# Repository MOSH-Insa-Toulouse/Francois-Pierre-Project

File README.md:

# Francois-Pierre-Project
## Projet capteur graphene
Projet de 4ème année Génie Physique, à l'INSA de Toulouse. Réalisation d'un capteur graphene de déformation. Le but est de mesurer la résistance et la tension du graphene sur une feuille de papier. Pour ce faire nous avons élaborer un capteur accessible à tous et simple d'utilisation sur arduino et App Inventor. Dans ce Git vous trouverez toute les ressources et information nécessaire pour comprendre le fonctionnement de notre capteur et pouvoir le réaliser chez vous.

## Sommaire

  - [1. Matériel requis](#1-Matériel-requis)
  - [2. Kicad](#2-Kicad)
      - [2.1 Création des empreintes et des composants](#21-Création-des-empreintes-et-des-composants)
      - [2.2 Création du PCB](#22-Création-du-PCB)
  - [3. Code Arduino](#3-code-arduino)
      - [3.1 Librairies utilisées](#31-Librairies-utilisées)
      - [3.2 Le code](#32-Le-code)
  - [4. Application Bluetooth](#4-application-Bluetooth)
  - [5. Banc de test](#5-Banc-de-test)
      - [5.1 Fonctionnement du banc](#51-Fonctionnement-du-banc)
      - [5.2 Code arduino](#52-Code-arduino)
  - [6. Datasheet](#6-datasheet)
  - [7. Contacte](#6-Contacte)

## 1. Matériel requis  

- Smartphone Androide 
- Carte Arduino Uno [info](https://www.arduino-france.com/review/arduino-uno/)
- Une plaque de cuivre pour shield. Ou bien des câbles de connexions
- Papier
- Crayon de papier
- Un module HC-05 (gestion du Bluetooth) [ici](https://fr.aliexpress.com/item/32496218488.html?src=google&albch=shopping&acnt=248-630-5778&isdl=y&slnk=&plac=&mtctp=&albbt=Google_7_shopping&aff_platform=google&aff_short_key=UneMJZVf&&albagn=888888&isSmbAutoCall=false&needSmbHouyi=false&albcp=11565796786&albag=115683794594&trgt=800756788306&crea=fr32496218488&netw=u&device=c&albpg=800756788306&albpd=fr32496218488&gclid=CjwKCAjwr_uCBhAFEiwAX8YJgRBUgtCF6S3dou6QC6xu91THwD-LvObxEluNS2bU644OLQE_p05mxxoCGZEQAvD_BwE&gclsrc=aw.ds)
- Un écran OLED [ici](https://www.google.com/aclk?sa=l&ai=DChcSEwjiwND8ltHvAhVc6u0KHTwOD0wYABAGGgJkZw&sig=AOD64_0E9f4FFmKPCGubT07_igBVagq6Cw&ctype=5&q=&ved=2ahUKEwi72sj8ltHvAhUSmRQKHRkPB9IQ9aACegQIARBK&adurl=)
- Un encodeur rotatif [ici](https://www.google.com/aclk?sa=l&ai=DChcSEwi_u8-dl9HvAhXC7e0KHZQrC94YABAEGgJkZw&sig=AOD64_0jWmans1feAKcjE1r1Iod4QknEqw&ctype=5&q=&ved=2ahUKEwi5kcadl9HvAhWl8uAKHZ9SAuUQ9aACegQIARBg&adurl=)
- Deux pince crocodile en cuivre
- Un transistor LTC1050 [ici](https://www.reichelt.com/fr/fr/amplificateurs-op-rationnels-unique-2-5-mhz-dil-8-ltc-1050-cn8-p10921.html) 

## 2. Kicad 

Kicad est un logiciel de conception pour l'électronique. Il permet de créer des schémas de circuit, visualiser des circuits en 3D, associer des empreintes au circuit. Dans notre cas, nous utilisons Kicad pour créer un shield pour notre carte Arduino Uno. Ce shield va nous permettre de monter nos composant directement sur la carte. Toute nos empreintes et plans de notre shield sont disponible dans [notre GIT](https://github.com/MOSH-Insa-Toulouse/Francois-Pierre-Project/tree/main/Shield)  

### 2.1 Création des empreintes et des composants

- Pour réaliser notre shield, nous avons dû créer une librairie d'empreinte pour nos composants. En effet ceux-ci n'étant pas disponible sur les librairies de Kicad nous avons donc créés des schémas et empreintes pour tous nos modules.

- *Capteur Graphite*

- *HC-05*

- *Encodeur Rotatoire*

- *OLED*

- *LTC1050*

### 2.2 Création du PCB

- Une fois les empreintes et les schématiques crées nous avons pu réaliser la schématique complète du circuit. Dans ce schéma vous pouvez retrouver nos modules ainsi que des composants éléctronique de base.

- *Schéma de notre circuit*

- Une fois la schématique finis nous avons pu allouer à chaque composants (résistance, capacité...) une empreinte. Nous avons ensuite visualisé sur l'éditeur de circuit imprimé notre PCB. Nous avons donc organisé nos composant pour qu'il tiennent sur le shield et que nous puissons router correctement et sur chaque pin les différents modules.

- Pour être sur du résultat que nous voulions nous avons pu visulaiser sur Gerber notre shield en 3D avec les composant dessus, à l'execption des module bluetooth, de l'encodeur, du capteur et du LTC qui n'ont pas d'empreinte 3D.

## 3. Code Arduino

### 3.1 Librairies utilisées

- Pour réaliser notre capteur, nous utilisons [trois librairies](https://github.com/MOSH-Insa-Toulouse/Francois-Pierre-Project/tree/main/Libairies%20Arduino). 
- La librairie ["Adafruit_BusIO"](https://github.com/MOSH-Insa-Toulouse/Francois-Pierre-Project/tree/main/Libairies%20Arduino/Adafruit_BusIO) qui permet de gérer le connexions en I2C et SPI
- Les librairies ["Adafruit_GFX_Library"](https://github.com/MOSH-Insa-Toulouse/Francois-Pierre-Project/tree/main/Libairies%20Arduino/Adafruit_GFX_Library) et ["Adafruit_SSD1306"](https://github.com/MOSH-Insa-Toulouse/Francois-Pierre-Project/tree/main/Libairies%20Arduino/Adafruit_SSD1306)qui permet de gérer notre écran OLED.

### 3.2 Le code

- [Le code arduino](https://github.com/MOSH-Insa-Toulouse/Francois-Pierre-Project/tree/main/Code-Capteur-Graphite) permet de gérer le capteur. Il récupère sur le pin analogique A0 la valeur de la tension du capteur. Grace à une analyse du circuit électronique, nous pouvons déterminer la résistance en fonction de cette tension. Le code affiche sur un écran OLED différents menus en fonction de si l'on appuie ou non sur l'encodeur rotatoire. Il y a un delay de 5ms entre chaque lecture analogique.

## 4. Application Bluetooth

- [L'application](https://github.com/MOSH-Insa-Toulouse/Francois-Pierre-Project/blob/main/TP5.apk) permet de recevoir sur le téléphone la mesure de la résistance et de la tension délivré par le capteur. Nous affichons les deux donnés et nous traçons un graphique de la variation de résistance avec une échelle ajustable. La carte Arduino et plus précisément le module Bluetooth envoie un octet de donnée au téléphone via les pins TX et RX. Cet octet contient à la fois des valeurs de résistance et de tension séparés par de ",". Chaque doublet de valeurs est lui séparé par des ";". Notre téléphone reçois donc "49,0.39;35,0.60;70,0.37" avec d'abord la valeur de résistance puis une valeur de tension. Le téléphone sépare donc chaque valeur et les affiches. Notre application traite les données sur un intervalle de 100ms. 

- *Code de l'application qui permet de séparer l'octet reçu et de séparer tension et résistance*

- Notre code a aussi une fonctionnalité qui enlève les variations trop importantes de résistance. En effet lors de nos tests notre téléphone recevait bien les valeurs affichées par le OLED, seulement nous avions aussi des valeurs intempestives qui ne correspondaient pas à une mesure (entre 1 et 9). Pour pallier ce problème, nous avons donc décider de ne pas prendre en compte les variations trop importantes.

- Pour finir nous avons rajouté une fonctionnalité qui permet à l'utilisateur de zoomer ou dezoomer sur le graphique.

- *Code APK permettant de Rescale le graphique*

- La face avant de notre application permet de choisir un module Bluetooth auquel se connecter (Cadre rouge), puis de régler l'échelle (bleu), de visualiser la variation de résistance (marron), et d'avoir les valeurs de résistance et tension en temps réelle (vert).

- *Face avant de notre application*

## 5. Banc de test

- Le banc de test est réalisé sur le logiciel de CAO FreeCad. Il nous est utile pour remplacer le banc de test initiale qui endommage et plie de manière irréversible la jauge de graphite. Le banc de test que nous avons imaginé permettrait donc de ré utiliser la même jauge plusieurs fois car celle-ci ne serait pas endommagé par les tests. Les fichier stl pour impression 3D sont [ici](https://github.com/MOSH-Insa-Toulouse/Francois-Pierre-Project/tree/main/Banc%20de%20test).

### 5.1 Fonctionnement du banc

- Le banc de test que nous avons imaginé permet de mesurer la déformation du capteur sans avoir à le toucher. Il est constitué de deux partie, le socle et la barre. Le servomoteur vient se positionner dans l'extrusion de la barre. Le disque présent sur l'autre côté vient lui se placer dans l'encoche du socle. Les pince crocodile ainsi que la jauge sont immobile grâce à l'encadrement dans lequel ils viennent s'insérer. Le servomoteur vient donc faire tourner la barre de bas en haut et nous récupérons les valeurs de résistances sur le terminal ou dans le fichier txt de notre téléphone.

- 
- 

- A l'inverse du banc de test initiale celui que nous avons imaginé n'a pas un rayon de courbure définis et connus. En revanche il est possible de connaitre le rayon de courbure avec la flèche F la distance S et R

### 5.2 Code arduino

- Le code arduino qui gèrent le banc de test permet d'afficher la résistance et la déformation en temps réelle. Il fait aussi s'activer le servomoteur, qui va bouger sur une rotation de 180 degrés. Cela nous permet de plier la jauge dans les deux sens. Étant donné que dans notre cas nous ne connaissons pas le rayon de courbure nous devons le calculer. Ceci est possible celons la manière suivante : 

- 

## 6. Datasheet

- [La datasheet](https://github.com/MOSH-Insa-Toulouse/Francois-Pierre-Project/blob/main/Datasheet.pdf) rédigé permet de comprendre les différentes caractéristiques de notre capteur. Veuillez la lire avant l'utilisation de celui-ci. 

## 7. Contacte

- Pour toute question concernant le capteur, l'application APK, le programme Arduino, le PCB ou pour tout complément d'information veuillez nous contacter par mail :
- Pierre CLARET pclaret@etud.insa-toulouse.fr
- François LEPETIT-AIMONT lepetit-@etud.insa-toulouse.fr

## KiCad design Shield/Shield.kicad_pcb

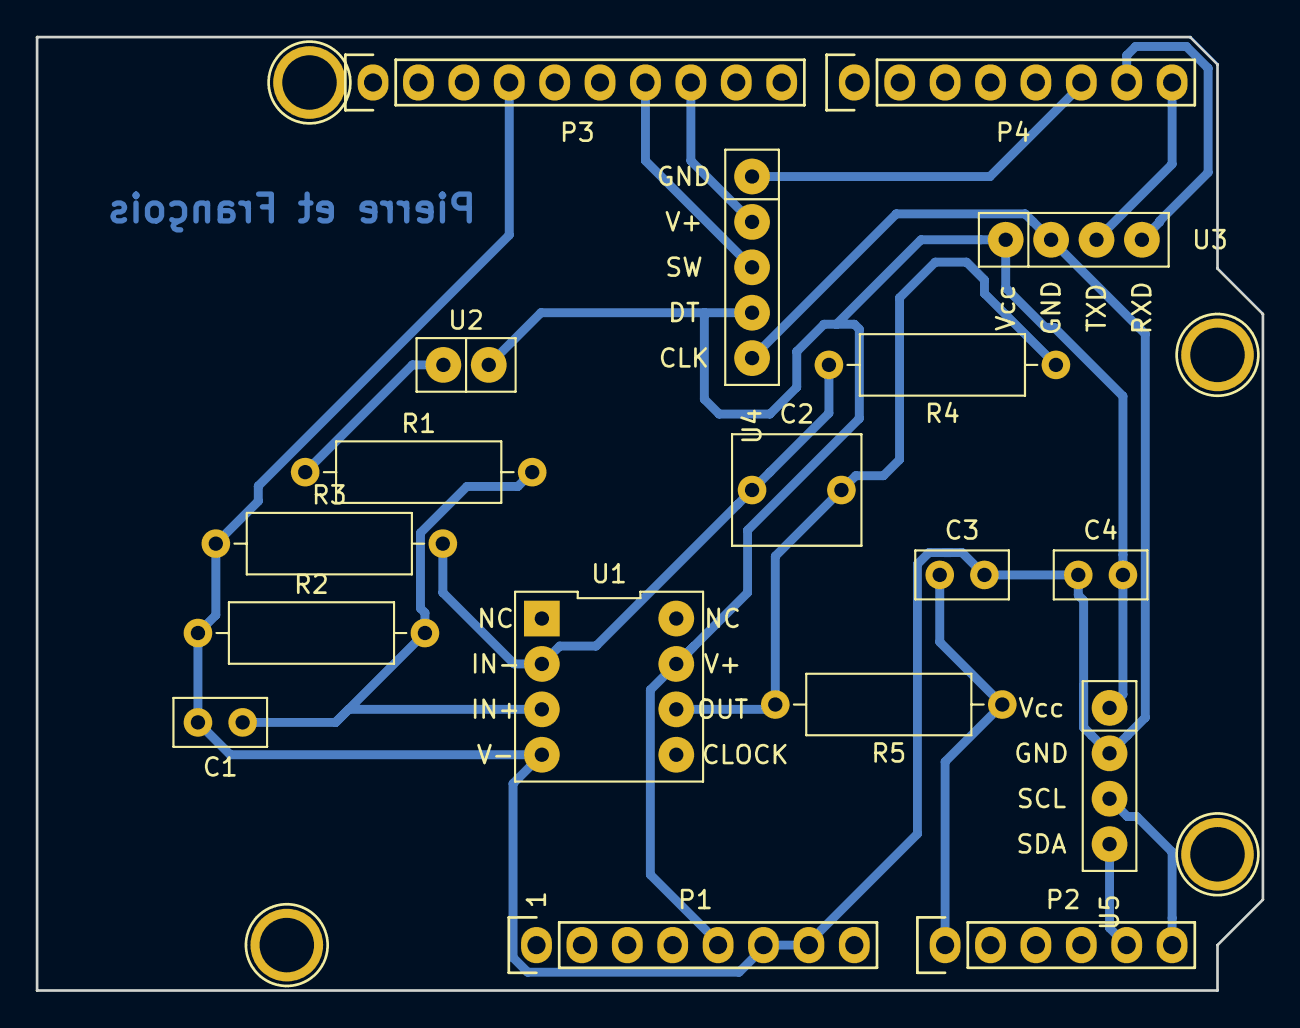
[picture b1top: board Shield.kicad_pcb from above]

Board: 2 copper layers, 68.6 x 53.3 mm, 22 parts (0 on the bottom side), 14 nets.

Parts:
C1, C4: 100n; C_Disc_D5.0mm_W2.5mm_P2.50mm
C2: 1u; C_Rect_L7.0mm_W6.0mm_P5.00mm
C3: 10n; C_Disc_D5.0mm_W2.5mm_P2.50mm
P1: Power; Socket_Strip_Arduino_1x08
P2: Analog; Socket_Strip_Arduino_1x06
P3: Digital; Socket_Strip_Arduino_1x10
P4: Digital; Socket_Strip_Arduino_1x08
P5, P6, P7, P8: CONN_01X01; Arduino_1pin
R1: 10k; R_Axial_DIN0309_L9.0mm_D3.2mm_P12.70mm_Horizontal
R2, R4: 100k; R_Axial_DIN0309_L9.0mm_D3.2mm_P12.70mm_Horizontal
R3, R5: 1k; R_Axial_DIN0309_L9.0mm_D3.2mm_P12.70mm_Horizontal
U1: LT1050; LTC1050
U2: Capteur_graphite
U3: HC-05
U4: KY-040
U5: OLED

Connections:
+5V: C4.2, P1.5, U1.7, U2.1, U3.1, U4.4, U5.1
ADC: C3.1, P2.1, R5.1
CLK: P4.6, U4.1
DT: P3.8, U4.2
GND: C1.2, C3.2, C4.1, P1.6, P1.7, P3.4, R2.1, R3.1, U1.4, U3.2, U4.5, U5.2
IN-: C2.1, R3.2, R4.2, U1.2
unnamed: C1.1, R1.2, R2.2, U1.3
OUT: C2.2, R4.1, R5.2, U1.6
RXD: P4.7, U3.4
SCL: P2.6, U5.3
SDA: P2.5, U5.4
SW: P3.7, U4.3
Sensor1: R1.1, U2.2
TXD: P4.8, U3.3

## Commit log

2021-02-05 README file def
2021-02-05 Création de dossier Arduino et Kicad
2021-02-05 Test avec Visual
2021-02-05 J'annule visual studio
2021-02-05 Test Image
2021-02-05 no message
2021-03-25 premier commit
2021-03-25 deuxieme commit
2021-03-26 Ajout d'images et datasheet
2021-03-28 Revert "Update README.md"
    This reverts commit b42ab934bcaa94375f9ab97ea1d8a2f3ec7afad9.
2021-03-28 Revert "Revert "Update README.md""
    This reverts commit 0cbf4e13695d90a62dc48f3df338c84e9c78908a.
2021-03-28 ReadMe du projet
2021-03-28 Kicad (PCB, routage...)
2021-03-28 Code Arduino du capteur
2021-03-28 Librairies Arduino
2021-03-28 Librairie d'image
2021-03-28 Datasheet du capteur
2021-04-29 Ajout banc de test
2021-04-29 Librairie images
2021-04-30 banc de test
2021-05-03 Librairies images
2021-06-15 Correction des fautes (mais pas toutes j'en ai peur...)
